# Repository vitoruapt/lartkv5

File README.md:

# lartkv5

## Description
The LAR toolkit is a software suite developed at LAR (http://lars.mec.ua.pt) since 2009 intended to support the software development involving robots, especially for the ATLAS project (http://atlas.web.ua.pt) and the PHUA project.
The initial versions (v1 and v2) used the CARMEN/IPC framework and later versions used ROS framework. Up to version 4, SVN was the version control support used, but with this version 5 (updated by 2014/2015) a migration to git was carried out.

The toolkit is quite a complex web of packages with many relations and interdependencies. A graphical view of these dependencies can be checked for version 4 (http://lars.mec.ua.pt/lartk4/) which is quite similar to this version 5.

## Using version v5
The lartkv5 was created using git in lar.mec.ua.pt server. The repository contains two folders, src and hardware.
Users from that repository must clone the repository

    git clone ssh: //USER@lars.mec.ua.pt/home/repositories/lar5 lar5

After cloned, it is necessary to start the ROS/catkin workspace inside the src folder, to create the main CMakeLists.txt (not under version control).

    cd src
    catkin_init_workspace

Next, you need to go up one folder and run catkin_make to create the build and devel folders along src and hardware folders. The build and devel folders must not be under version control.

    cd ..
    catkin_make

The repository compilation should work completely.
At first, it is possible to install some dependencies (**ros-indigo-sound-play**), but the packages with complicated manual install dependencies will not be compiled.
During the first phase of the compilation, warnings will appear about which packages will not be compiled.
Some packages will not compile because they issue some errors that I [Jorge Almeida] could not solve, in those cases I adjusted the `cmakelist` to avoid compilation attempts.
I sent to the professor the google spreadsheet file with the problems encountered in the migration.

## Updates by V. Santos, 08-Mar-2015,12:56
To enable the compilations of some modules, the following packages were needed:

* sudo apt-get install ros-indigo-sound-play
* sudo apt-get install libudev-dev
* sudo apt-get install libkml-dev              #detected by cmake
* sudo apt-get install libdmtx-dev             #detected by cmake
* sudo apt-get install gtkmm-3.0
* sudo apt-get install ros-indigo-gps-common
* sudo apt-get install libgraphviz-dev         #detected by cmake
* sudo apt-get install libcgal-dev             #detected by cmake

Also corrected several cases of:
 catkin_package () include dir 'include' does not exist relative to
   '/home/vitor/SWproj/lar5/src/sensors/odometer'
   Just edit the local CMakeLists.txt and comment a line of the kind:
 INCLUDE_DIRS include

in catkin_package specific configuration

## Further issues
It would be interesting to adopt a workflow based on branches and not centralized as it existed until now
    https://www.atlassian.com/git/tutorials/comparing-workflows/feature-branch-workflow
has a comparison of the various workflows and how they work in git, and can be useful.

New branches are simple to create:

    git checkout -b NEWBRANCH

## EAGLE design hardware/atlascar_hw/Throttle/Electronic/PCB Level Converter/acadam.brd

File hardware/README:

README file for LAR toolkit Hardware component
================================================

This directory includes information and data related
to the hardware involved in the development of the 
robotic platforms and their several subsystems.
Each robot platform has its own directory.
Also, a common_hw directory is created for hardware
solutions that are not limited to a single robot platform.

You can create a new subsystem documentation folder
by running the script CreateNewHardwareSubsystem.sh

Follows more details about the strucuture of that
subsystem folder.

On each robot platform, each respective subsystem will be installed
in one directory and on each directory there will be files and directories
concerning the hardware involved (mechanical, electrical,
drawing schematics, firmwares, microcontrollers code, etc.)
Suggestions for standard names of files/directories to create:

	<subsystem>_index.html - File with a general description of the subsystem with explanations and links to the remainder of the directory
	Mechanical             - Folder with mechanical drawings and CAD models
	Electrical             - Folder with electrical and electronics circuits (schematics, PCBs, component lists, etc.)
	Code                   - Code for microcontrollers and other firmware (must contain Makefiles or other instructions to build the binaries)

The <subsystem>_index.html is a HTML file that should have
common areas in order to be uniform among authors (see below).
[In a near future, a XML template should be the base to build 
this HTML file.]
There is also a file named subsystemId.js used for generic 
definitions about a given susbsystem. This is a javascript code 
included by the main html file. This code includes the name of
the subsystem, author of documentation and date of elaboration. 
Adjust this file accordingly.

The following sections/fields are required for the HTML file
	Title
	Brief description
	System operation 
		[Long description]
	Mechanical components 
		[conceptual mechanism, Drawings of fixing and supporting systems...]
	Electrical circuits 
		[Electrical circuits of the devices]
	Firmware and similar code 
		[Describe what programs and environments are used alogn with links to relevant code]
	Maintenance 
		[Specific instructions for technitians and engineers]

	Last update information (Author, date)

On each section, include when applicable links and images.

------------------------------------------------------------------

Each of the mentioned directories may have several subdirectories
in case the subsystem has several valid approaches, or if 
it is convenient to split the subsystem in smaller parts.
That should however be avoided to keep the system simple.

These are the current platforms of LAR3 toolkit
	atlascar_hw
	atlasmv_hw
	atlas20XX_hw
	arenabots_hw
	humanoid_hw
	common_hw

This is an example of a starting partial structure 
of the hardware subdirectory of LAR3 toolkit:

|-- atlascar_hw
|   |-- PedalActuation
|   |   |-- Code
|   |   |-- Electrical
|   |   |-- Mechanical
|   |   `-- pedalactuation_index.html
|   |-- DriveWheelActuation
|   `-- Throttle
|-- atlasmv_hw
|-- atlas20XX_hw
|-- arenabots_hw
|-- humanoid_hw
`-- README

============================================================================

SUMMARY OF PROCEDURE TO CREATE THE HARDWARE DOCUMENTATION.
[Inspire yourself for example in the "PedalActuation" directory in atlascar_hw]

	1-Locate the base harware platform directory (atlascar_hw, humanoid_hw, ...)
	2-Inside it, create a directory for the given subsystem (if not yet existing)
	3-Create/adapt the following files/directories
		<subsystem>_index.html (file)
        	Mechanical             (folder)
        	Electrical             (folder)
        	Code                   (folder)
	4-Adjust the subsystemId.js file with specific details
	5-Fill in the previous folders with associated documents and images

-

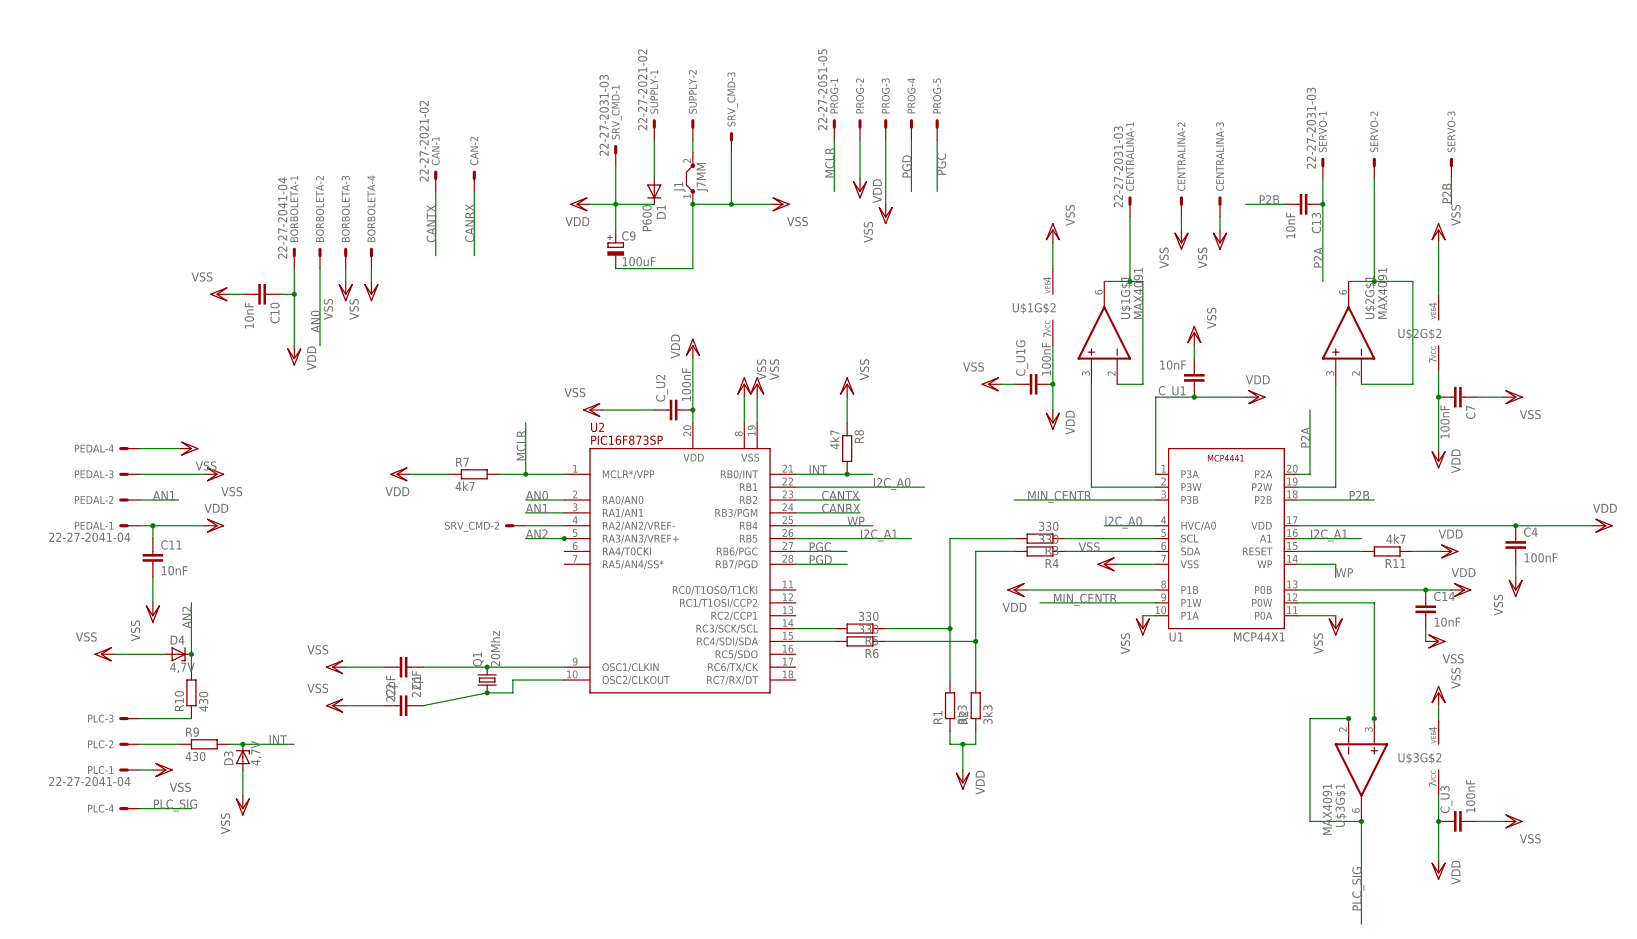
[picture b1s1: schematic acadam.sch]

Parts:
BORBOLETA: 22-27-2041-04; 6410-04
C1, C2: 22pF; C0603
C4, C7: 100nF; C0805
C9: 100uF; E2,5-5
C10, C11, C13, C14: 10nF; C0805
CAN: 22-27-2021-02; 6410-02
CENTRALINA: 22-27-2031-03; 6410-03
C_U1: 10nF; C0805
C_U1G, C_U2, C_U3: 100nF; C0805
D1: P600; P6-15
D3, D4: 4,7V; DO34Z7
J1: J7MM; 07
PEDAL: 22-27-2041-04; 6410-04
PLC: 22-27-2041-04; 6410-04
PROG: 22-27-2051-05; 6410-05
Q1: 20Mhz; HC49/S
R1, R2: 3k3; 0204/5
R3, R4, R5, R6: 330; 0204/5
R7, R8, R11: 4k7; 0204/5
R9, R10: 430; 0204/5
SERVO: 22-27-2031-03; 6410-03
SRV_CMD: 22-27-2031-03; 6410-03
SUPPLY: 22-27-2021-02; 6410-02
U1: MCP44X1; TSSOP20
U2: PIC16F873SP; DIL28-3
U$1, U$2, U$3: MAX4091; SO-08

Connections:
AN0: BORBOLETA.2, U2.2 (RA0/AN0)
AN1: PEDAL.2, U2.3 (RA1/AN1)
AN2: D4.C, R10.2, U2.5 (RA3/AN3/VREF+)
CANRX: CAN.2, U2.24 (RB3/PGM)
CANTX: CAN.1, U2.23 (RB2)
I2C_A0: U1.4 (HVC/A0), U2.22 (RB1)
I2C_A1: U1.16 (A1), U2.26 (RB5)
INT: D3.C, R8.2, R9.2, U2.21 (RB0/INT)
MCLR: PROG.1, R7.2, U2.1 (MCLR*/VPP)
MIN_CENTR: U1.3 (P3B), U1.9 (P1W)
unnamed: D1.A, SUPPLY.1
unnamed: J1.2, SUPPLY.2
unnamed: U1.19 (P2W), U$2.3 (+IN)
unnamed: SERVO.2, U$2.2 (-IN), U$2.6 (OUT)
unnamed: U1.2 (P3W), U$1.3 (+IN)
unnamed: CENTRALINA.1, U$1.2 (-IN), U$1.6 (OUT)
unnamed: U1.12 (P0W), U$3.3 (+IN)
unnamed: SRV_CMD.2, U2.4 (RA2/AN2/VREF-)
unnamed: R1.2, R3.2, R5.1
unnamed: R2.2, R4.2, R6.1
unnamed: C1.1, Q1.2, U2.9 (OSC1/CLKIN)
unnamed: R3.1, U1.5 (SCL)
unnamed: R4.1, U1.6 (SDA)
unnamed: R6.2, U2.15 (RC4/SDI/SDA)
unnamed: R5.2, U2.14 (RC3/SCK/SCL)
unnamed: C2.2, Q1.1, U2.10 (OSC2/CLKOUT)
unnamed: R11.2, U1.15 (RESET)
P2A: C13.1, SERVO.1, U1.20 (P2A)
P2B: C13.2, SERVO.3, U1.18 (P2B)
PGC: PROG.5, U2.27 (RB6/PGC)
PGD: PROG.4, U2.28 (RB7/PGD)
PLC_A_M: PLC.2, R9.1
PLC_REF: PLC.3, R10.1
PLC_SIG: PLC.4, U$3.2 (-IN), U$3.6 (OUT)
VDD: BORBOLETA.1, C4.1, C7.2, C9.+, C10.1, C11.1, C14.1, C_U1.1, C_U1G.2, C_U2.2, C_U3.1, D1.C, PEDAL.1, PROG.2, R1.1, R2.1, R7.1, R11.1, SRV_CMD.1, U1.1 (P3A), U1.8 (P1B), U1.13 (P0B), U1.17 (VDD), U2.20 (VDD), U$1.7 (VCC), U$2.7 (VCC), U$3.7 (VCC)
VSS: BORBOLETA.3, BORBOLETA.4, C1.2, C2.1, C4.2, C7.1, C9.-, C10.2, C11.2, C14.2, CENTRALINA.2, CENTRALINA.3, C_U1.2, C_U1G.1, C_U2.1, C_U3.2, D3.A, D4.A, J1.1, PEDAL.3, PEDAL.4, PLC.1, PROG.3, R8.1, SRV_CMD.3, U1.7 (VSS), U1.10 (P1A), U1.11 (P0A), U2.8 (VSS), U2.19 (VSS), U$1.4 (VEE), U$2.4 (VEE), U$3.4 (VEE)
WP: U1.14 (WP), U2.25 (RB4)

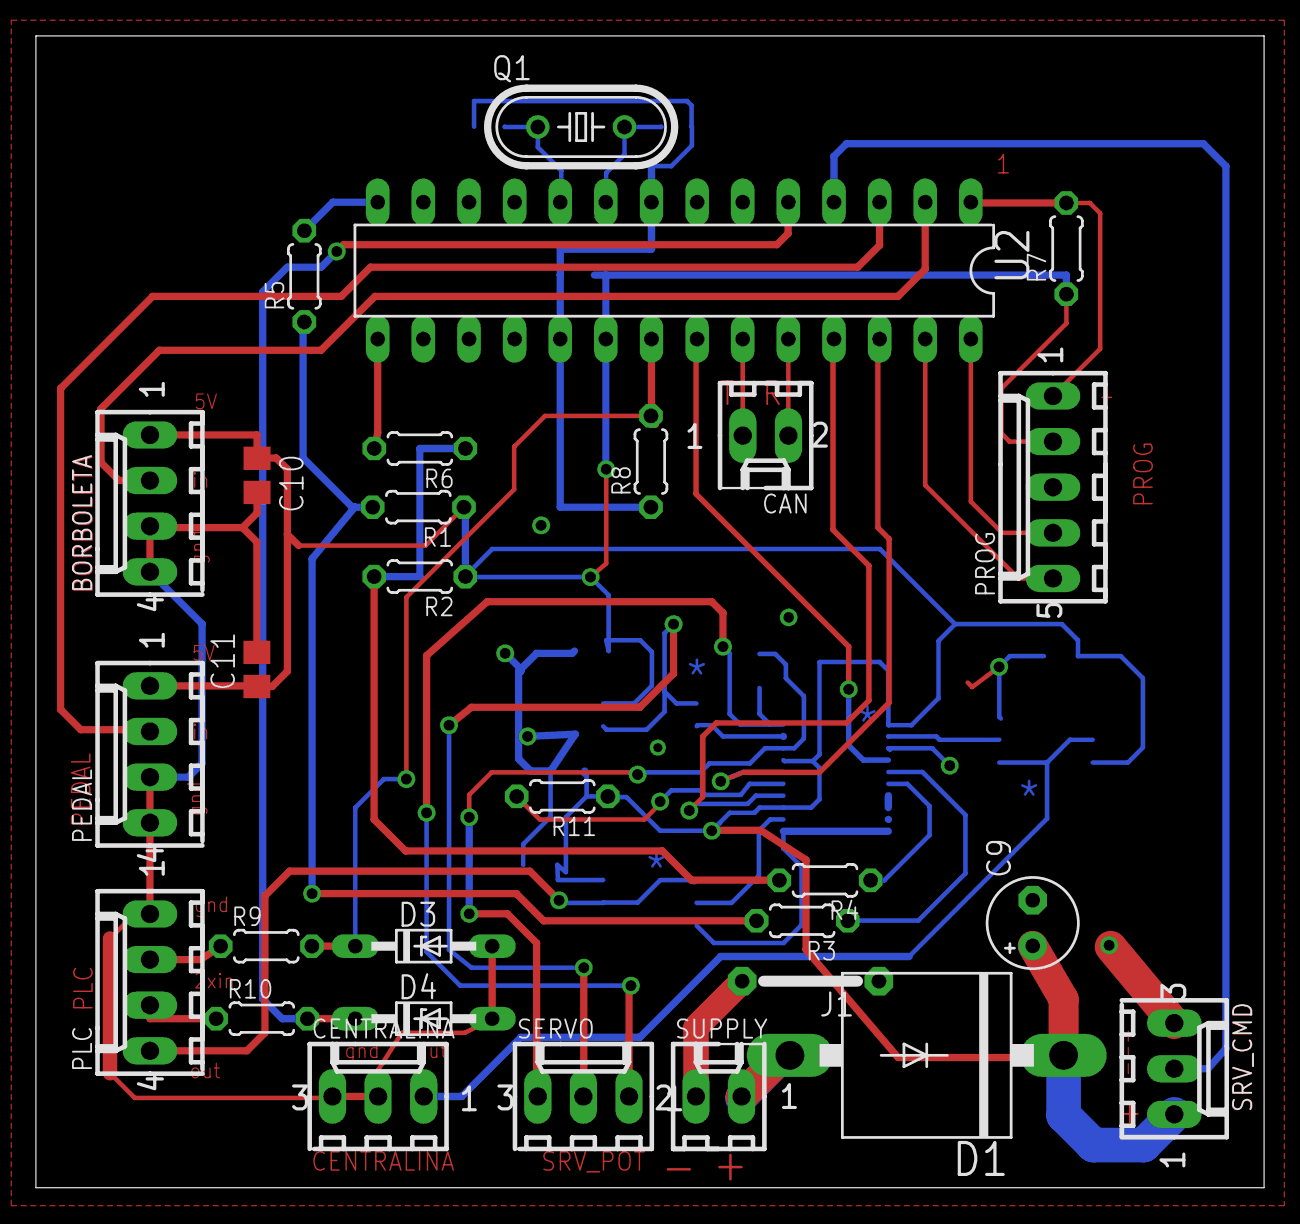
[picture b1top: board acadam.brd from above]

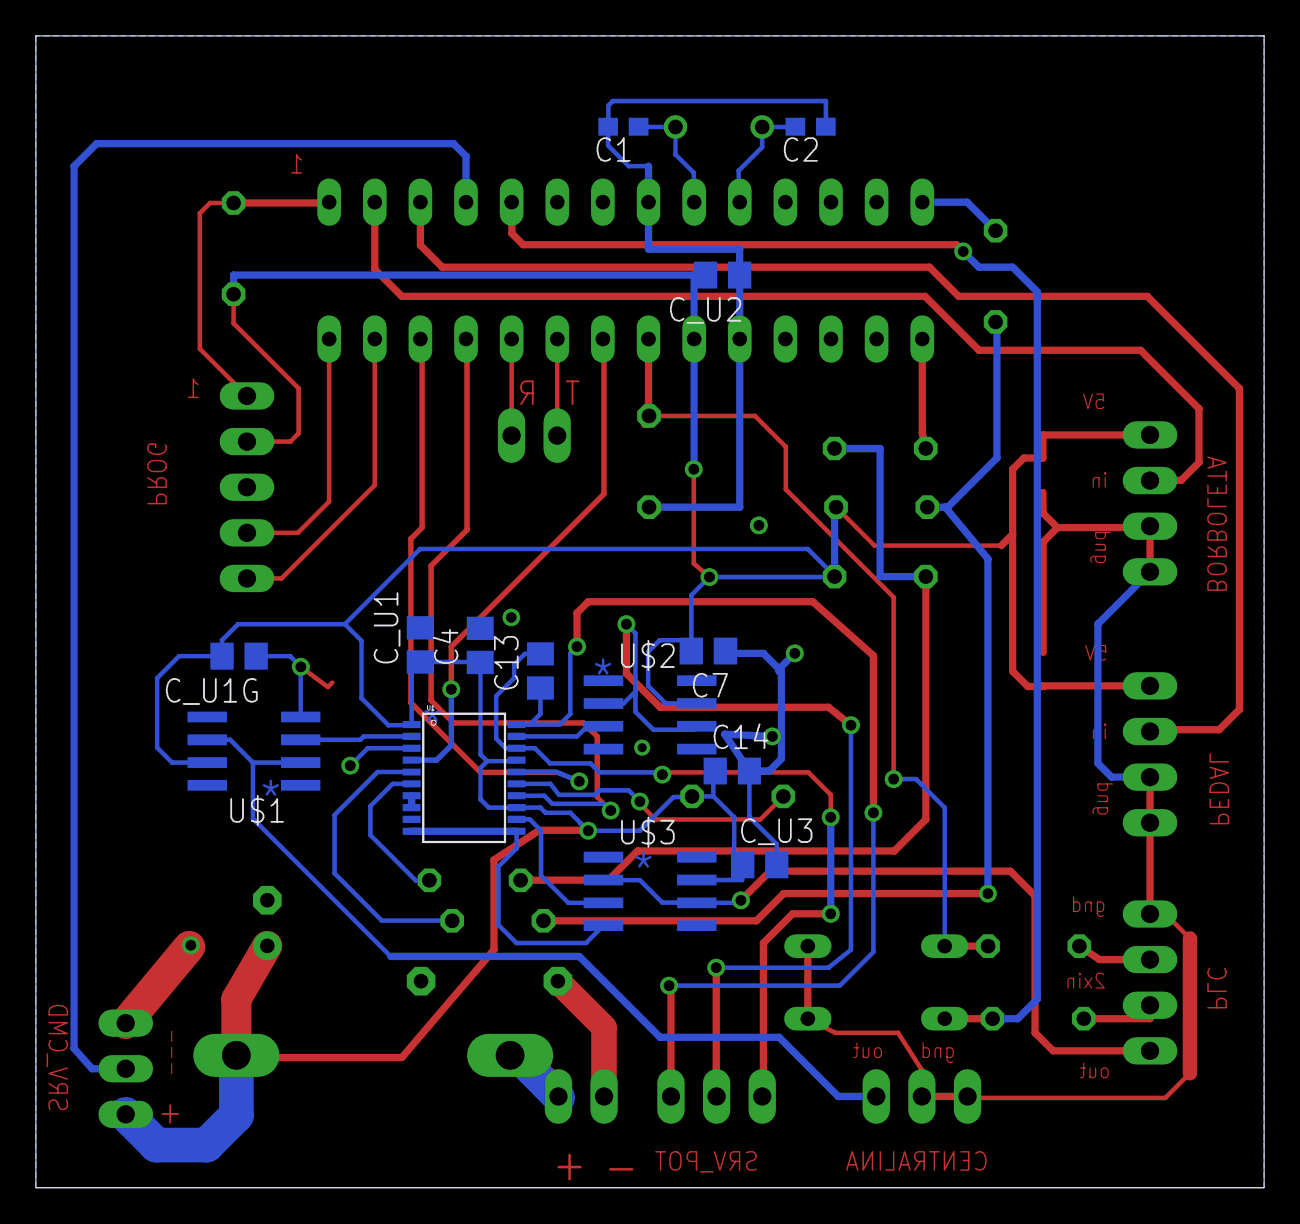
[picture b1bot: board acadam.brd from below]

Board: 2 copper layers, 68.4 x 64.1 mm, 43 parts (14 on the bottom side), 37 nets.

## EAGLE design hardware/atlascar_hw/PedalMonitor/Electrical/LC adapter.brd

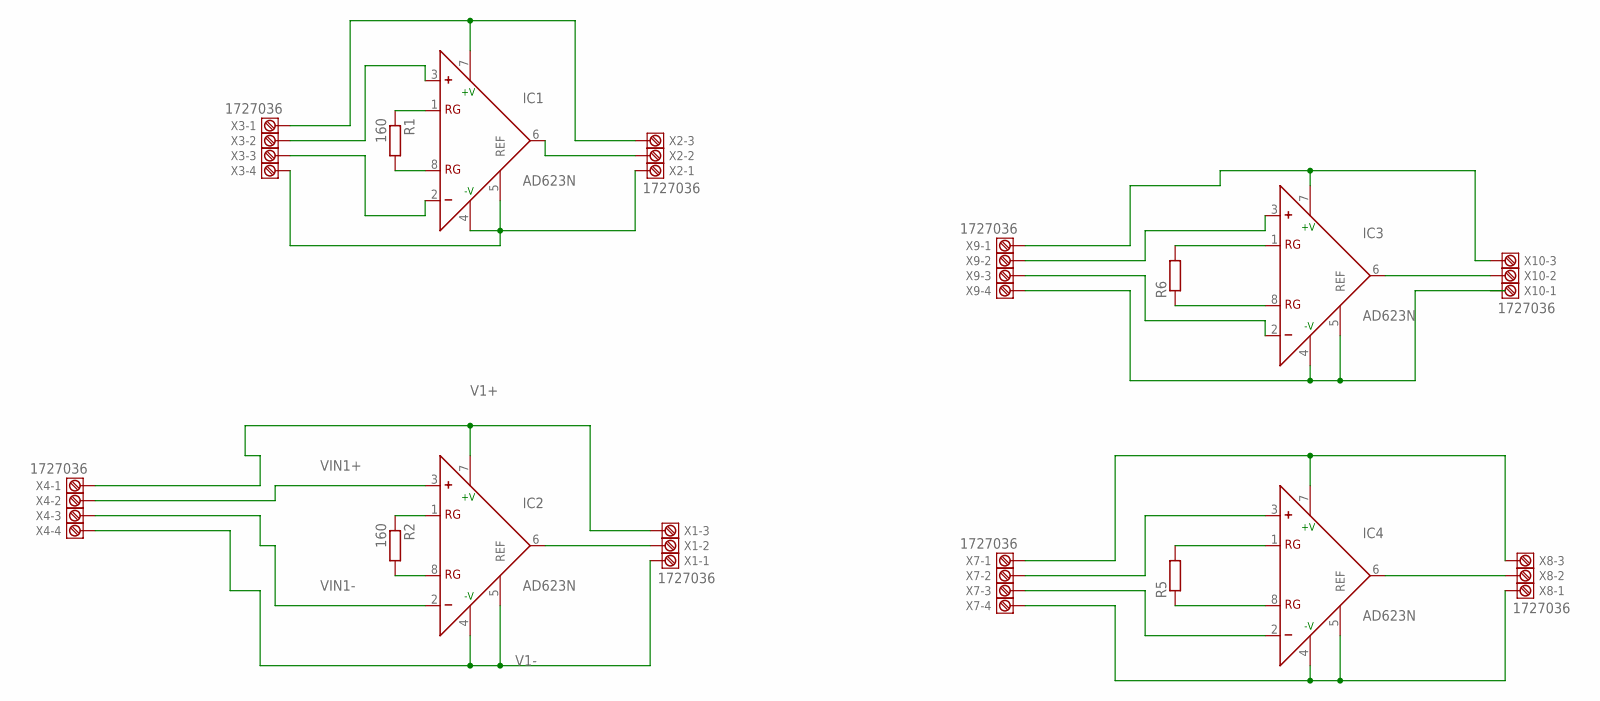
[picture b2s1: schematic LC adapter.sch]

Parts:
IC1, IC2, IC3, IC4: AD623N; DIL08
R1, R2: 160; 0204/7
R5, R6: R-EU_0204/7; 0204/7
X1, X2, X3, X4, X7, X8, X9, X10: 1727036

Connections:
unnamed: IC1.1 (RG), R1.1
unnamed: IC1.8 (RG), R1.2
unnamed: IC2.1 (RG), R2.1
unnamed: IC2.8 (RG), R2.2
unnamed: IC1.7 (+V), X2.3, X3.1
unnamed: IC1.6 (OUT), X2.2
unnamed: IC1.4 (-V), IC1.5 (REF), X2.1, X3.4
unnamed: IC3.1 (RG), R6.2
unnamed: IC1.3 (+), X3.2
unnamed: IC1.2 (-), X3.3
unnamed: IC3.8 (RG), R6.1
unnamed: IC2.6 (OUT), X1.2
unnamed: IC3.3 (+), X9.2
unnamed: IC3.2 (-), X9.3
unnamed: IC3.7 (+V), X9.1, X10.3
unnamed: IC3.4 (-V), IC3.5 (REF), X9.4
unnamed: IC4.1 (RG), R5.2
unnamed: IC4.8 (RG), R5.1
unnamed: IC3.6 (OUT), X10.2
unnamed: IC4.6 (OUT), X8.2
unnamed: IC4.7 (+V), X7.1, X8.3
unnamed: IC4.4 (-V), IC4.5 (REF), X7.4, X8.1
unnamed: IC4.2 (-), X7.3
unnamed: IC4.3 (+), X7.2
V1+: IC2.7 (+V), X1.3, X4.1
V1-: IC2.4 (-V), IC2.5 (REF), X1.1, X4.4
VIN1+: IC2.3 (+), X4.2
VIN1-: IC2.2 (-), X4.3

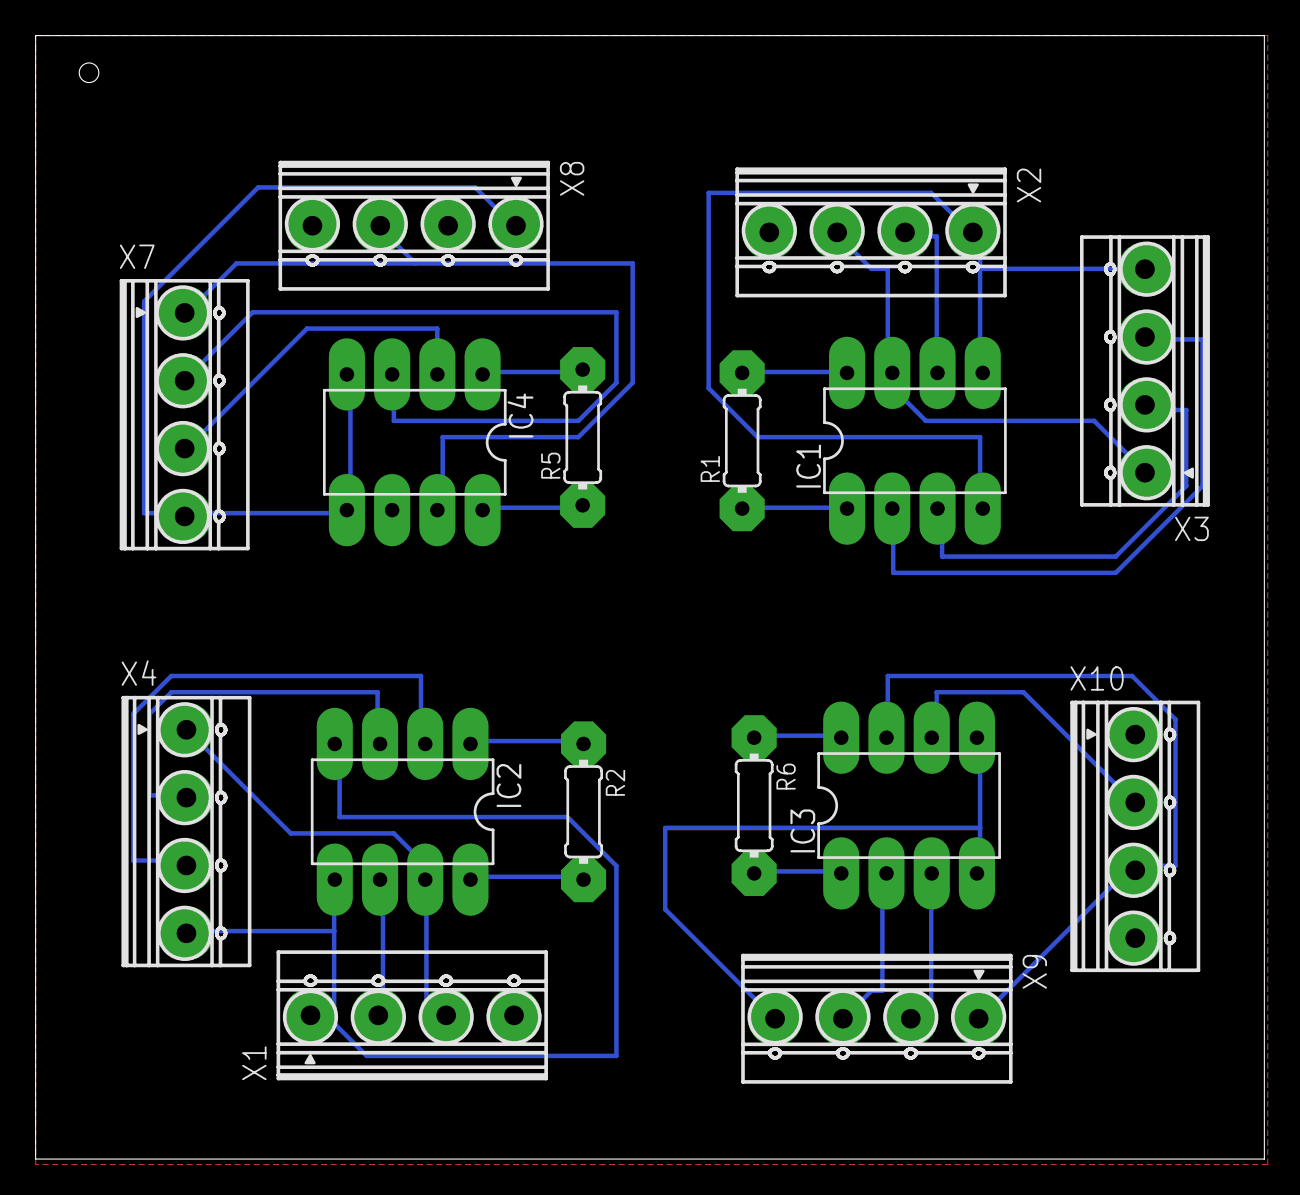
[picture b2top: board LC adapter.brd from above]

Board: 2 copper layers, 69.0 x 63.1 mm, 16 parts (0 on the bottom side), 27 nets.

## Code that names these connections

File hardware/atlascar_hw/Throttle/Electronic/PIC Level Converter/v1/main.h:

/*
 * File:   main.h
 * Author: dgameiro
 *
 * Created on 16 de Fevereiro de 2012, 10:37
 */

#ifndef main_H
#define main_H

#define _XTAL_FREQ 20

#include <p18cxxx.h>
#include <delays.h>
#include <adc.h>
#include <timers.h>
#include <i2c.h>
#include <portb.h>
#include <math.h>

#include "auxfunc.h"
//TODO: USER CODE

/*
 * place for DEFINES
 */

/*********************************
 *      ADC
 *********************************/
#define ADC_RES 1024.0    //10 bits adc
#define CH_THROTTLE ADC_CH0
#define CH_PEDAL ADC_CH1
#define CH_PLC ADC_CH3
#define VDD 5.0         //circuit supply voltage
//when the throtle is the minimun and maximum
//the values that will be imposed to the car EPS
//must be specified by the two defines. minimum value and maximum value
#define MIN_VOLT_CENTRALINA 2.5
#define MAX_VOLT_CENTRALINA 4.7

//value read from adc, value source will depend on man_auto state
unsigned int adc_new_pos;
unsigned int adc_old_pos;
unsigned int adc_pos_dif;
unsigned int adc_throttle;



/*********************************
 *      POTENTIOMETERS
 *********************************/
#define POT_RES 128.0     //7 bits potentiometer
#define I2C_POT_ADDRESS 0b01011001
#define I2C_WRITE_BIT 0b11111110
#define I2C_READ_BIT 0b11111111
#define I2C_POT_A0 PORTBbits.RB1
#define I2C_POT_A1 PORTBbits.RB5
#define I2C_POT_WP PORTBbits.RB4


#define MSG_MEM_TCON0 0x4c
#define MSG_MEM_TCON1 0xAd
#define MSG_MEM_STAT 0x5c
#define MSG_MEM_WP0 0x2c
#define MSG_MEM_WP1 0x3c
#define MSG_MEM_WP2 0x8c
#define MSG_MEM_WP3 0x9c

#define MSG_MEM_EE0 0b10111100  //0xbd
#define MSG_MEM_EE1 0xcc
#define MSG_MEM_EE2 0xdc
#define MSG_MEM_EE3 0xec
#define MSG_MEM_EE4 0xfc


#define CMD_READ 0b11111111
#define CMD_INC 0b11110111
#define CMD_DEC 0b11111011
#define CMD_WRITE 0b11110011

float r_pot_adc;
unsigned char man_auto;
unsigned char pot_values[8];
unsigned char pot_servo_ctrl;
unsigned char pot_plc;
unsigned char pot_car;
unsigned char pot_ref_min_car;
unsigned char max_centralina_pot;


/*********************************
 *      SERVO CTRL
 *********************************/
#define SRV_CMD PORTAbits.RA2
//values of pwm control are in s
#define MIN_SRV_PWM 1.0E-3        //1ms
#define MAX_SRV_PWM 2.0E-3        //2m
#define PERIOD_SRV_PWM 20.0E-3    //20ms


unsigned int pwm_period;
unsigned int duty_value;
int b_adc2timer;
float m_adc2timer;
unsigned int min_pwm_duty;
unsigned int max_pwm_duty;


/*********************************
 *      TIMER0
 *********************************/
// prescaler values
// 0 - 1:2  |   4 - 1:32
// 1 - 1:4  |   5 - 1:64
// 2 - 1:8  |   6 - 1:128
// 3 - 1:16 |   7 - 1:256
#define TMR0_PRE_SCALER 5
#define TMR0_VAL 250

float t_osc;
float t_osc_pres;
unsigned int counter_pwm;


//functions
void high_isr(void); //hight interrupt service routine
void low_isr(void); //low interrupt service routine
void init_pic(void);//function just to setup microcontroller
void init_pot(unsigned char address);//function to initialize the digital potentiometer
void send_pot_values(unsigned char address, const unsigned char* msg);//used to sent new potentiometer config
#endif

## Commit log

2017-10-12 First commit to GitHub - October 2017
2017-10-12 First full upload
